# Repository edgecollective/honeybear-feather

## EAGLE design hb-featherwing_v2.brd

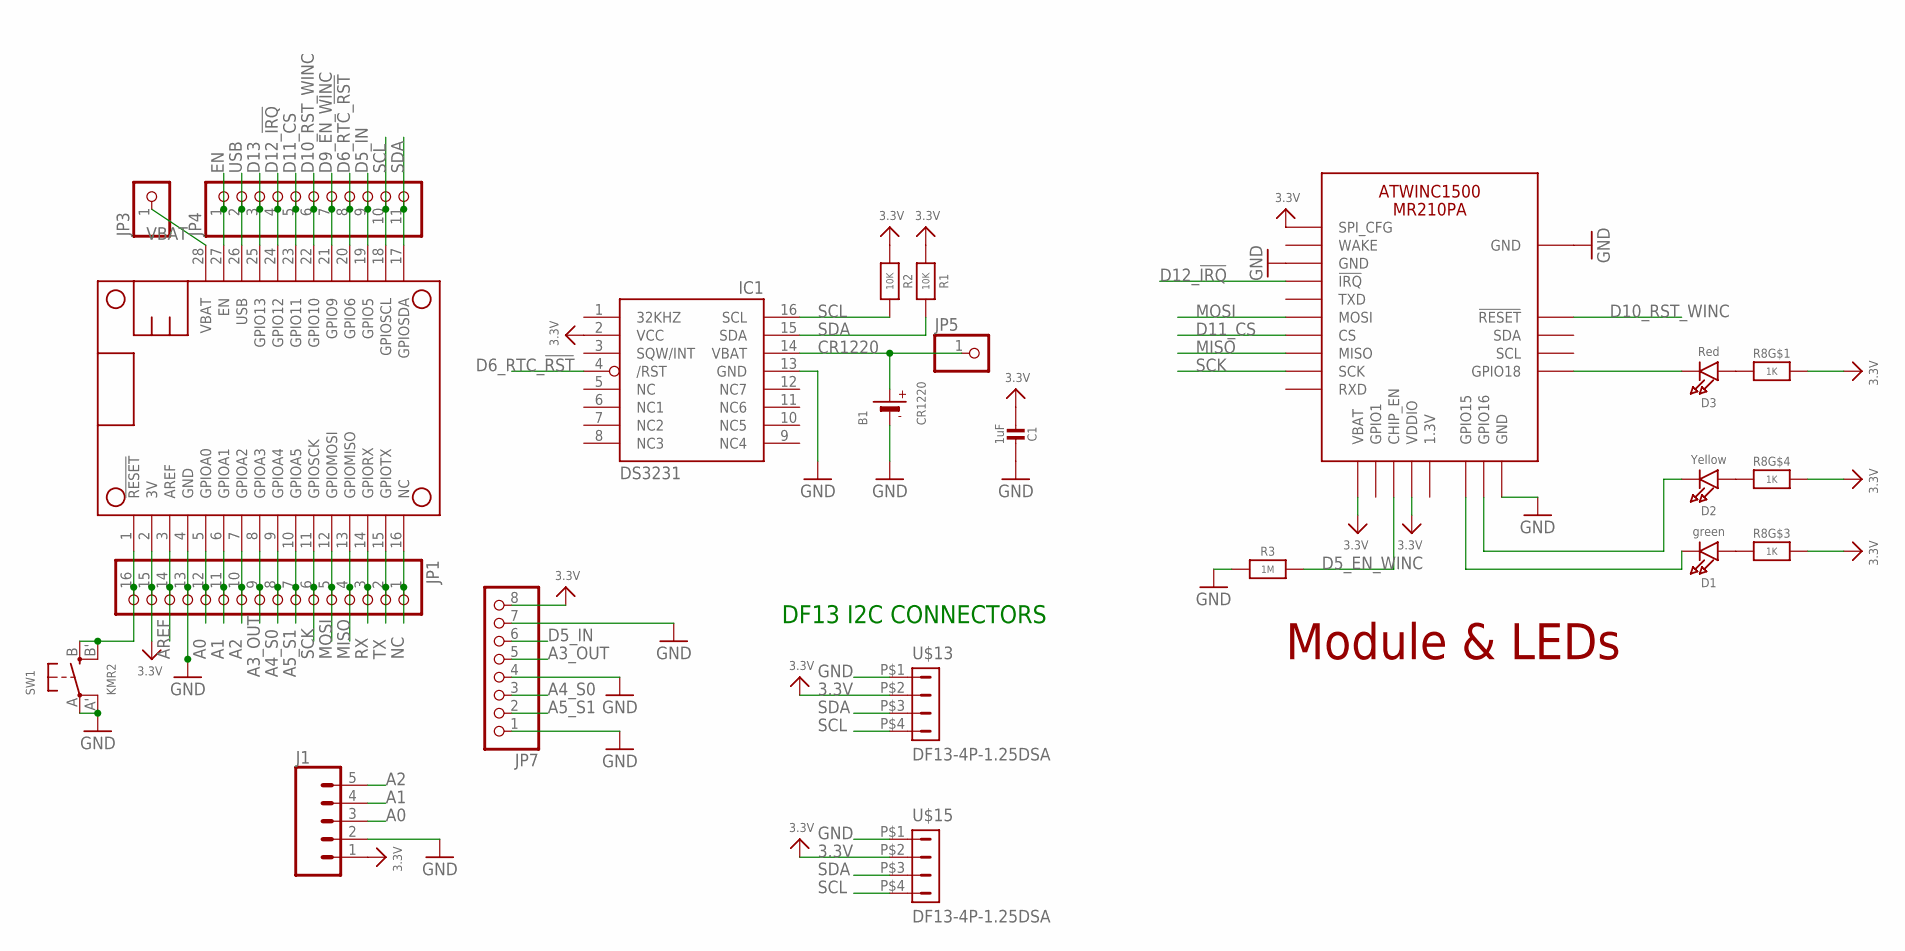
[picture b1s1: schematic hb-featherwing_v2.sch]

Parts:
B1: CR1220; CR1220-2
C1: 1uF; 0805-NO
D1: green; CHIPLED_0805_NOOUTLINE
D2: Yellow; CHIPLED_0805_NOOUTLINE
D3: Red; CHIPLED_0805_NOOUTLINE
IC1: DS3231/SO; SO16W
J1: CONN_05; 1X05
JP1: HEADER-1X16ROUND; 1X16_ROUND
JP3, JP5: HEADER-1X1ROUND; 1X01_ROUND
JP4: HEADER-1X11; 1X11_ROUND
JP7: PINHD-1X8BIG; 1X08-BIG
MS1: MICROSHIELD_NODIM; MICROSHIELD_DIM
R1, R2: 10K; 0805-NO
R3: 1M; 0805-NO
R8: 1K; RESPACK_4X0603
SW1: KMR2; BTN_KMR2_4.6X2.8
U$7: ATWINC1500_MR210PB; ATWINC1500_MR210PA
U$13, U$15: DF13-4P-1.25DSA

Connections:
3.3V: C1.2, IC1.2 (VCC), J1.1, JP1.15, JP7.8, MS1.2 (3V), R1.1, R2.1, R8.5 (2), R8.6 (2), R8.8 (2), U$7.J10 (SPI_CFG), U$7.J20 (VBAT), U$7.J23 (VDDIO), U$13.P$2 (2), U$15.P$2 (2)
A0: J1.3, JP1.12, MS1.5 (GPIOA0)
A1: J1.4, JP1.11, MS1.6 (GPIOA1)
A2: J1.5, JP1.10, MS1.7 (GPIOA2)
A3_OUT: JP1.9, JP7.5, MS1.8 (GPIOA3)
A4_S0: JP1.8, JP7.3, MS1.9 (GPIOA4)
A5_S1: JP1.7, JP7.2, MS1.10 (GPIOA5)
AREF: JP1.14, MS1.3 (AREF)
CR1220: B1.+, IC1.14 (VBAT), JP5.1
D5_EN_WINC: R3.2, U$7.J22 (CHIP_EN)
D5_IN: JP4.9, JP7.6, MS1.19 (GPIO5)
D6_RTC_!RST: IC1.4 (/RST), JP4.8, MS1.20 (GPIO6)
D9_EN_WINC: JP4.7, MS1.21 (GPIO9)
D10_RST_WINC: JP4.6, MS1.22 (GPIO10), U$7.J4 (!RESET)
D11_CS: JP4.5, MS1.23 (GPIO11), U$7.J16 (CS)
D12_!IRQ: JP4.4, MS1.24 (GPIO12), U$7.J13 (!IRQ)
D13: JP4.3, MS1.25 (GPIO13)
EN: JP4.1, MS1.27 (EN)
GND: B1.-, C1.1, IC1.13 (GND), J1.2, JP1.13, JP7.1, JP7.4, JP7.7, MS1.4 (GND), R3.1, SW1.A, SW1.A' (P1), U$7.J9 (GND), U$7.J12 (GND), U$7.J28 (GND), U$7.MTGND (GND), U$13.P$1 (1), U$15.P$1 (1)
GPIO15: D1.C, U$7.J26 (GPIO15)
GPIO16: D2.C, U$7.J27 (GPIO16)
GPIO18: D3.C, U$7.J1 (GPIO18)
MISO: JP1.4, MS1.13 (GPIOMISO), U$7.J17 (MISO)
MOSI: JP1.5, MS1.12 (GPIOMOSI), U$7.J15 (MOSI)
unnamed: D3.A, R8.1
unnamed: D2.A, R8.4 (1)
unnamed: D1.A, R8.3 (1)
unnamed: JP1.16, MS1.1 (!RESET), SW1.B (S), SW1.B' (S1)
NC: JP1.1, MS1.16 (NC)
RX: JP1.3, MS1.14 (GPIORX)
SCK: JP1.6, MS1.11 (GPIOSCK), U$7.J18 (SCK)
SCL: IC1.16 (SCL), JP4.10, MS1.18 (GPIOSCL), R2.2, U$13.P$4 (4), U$15.P$4 (4)
SDA: IC1.15 (SDA), JP4.11, MS1.17 (GPIOSDA), R1.2, U$13.P$3 (3), U$15.P$3 (3)
TX: JP1.2, MS1.15 (GPIOTX)
USB: JP4.2, MS1.26 (USB)
VBAT: JP3.1, MS1.28 (VBAT)

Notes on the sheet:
Module & LEDs
DF13 I2C CONNECTORS

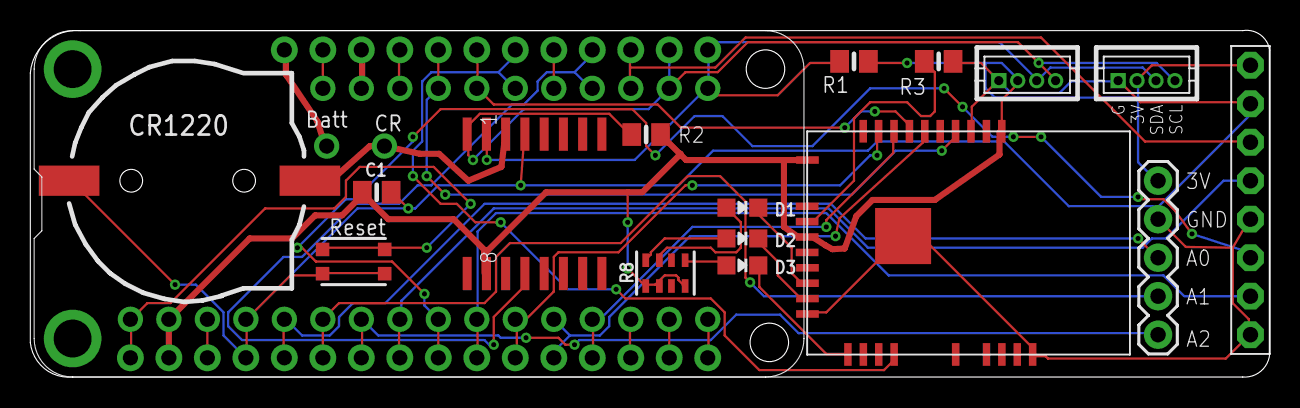
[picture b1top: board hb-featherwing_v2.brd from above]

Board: 2 copper layers, 81.8 x 22.9 mm, 21 parts (0 on the bottom side), 36 nets.

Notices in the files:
parts and their libraries:
microbuilder: This work is placed in the public domain, and may be freely used for commercial and non-commercial work with the following conditions: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
SparkFun-Connectors: Licensing: Creative Commons ShareAlike 4.0 International - https://creativecommons.org/licenses/by-sa/4.0
